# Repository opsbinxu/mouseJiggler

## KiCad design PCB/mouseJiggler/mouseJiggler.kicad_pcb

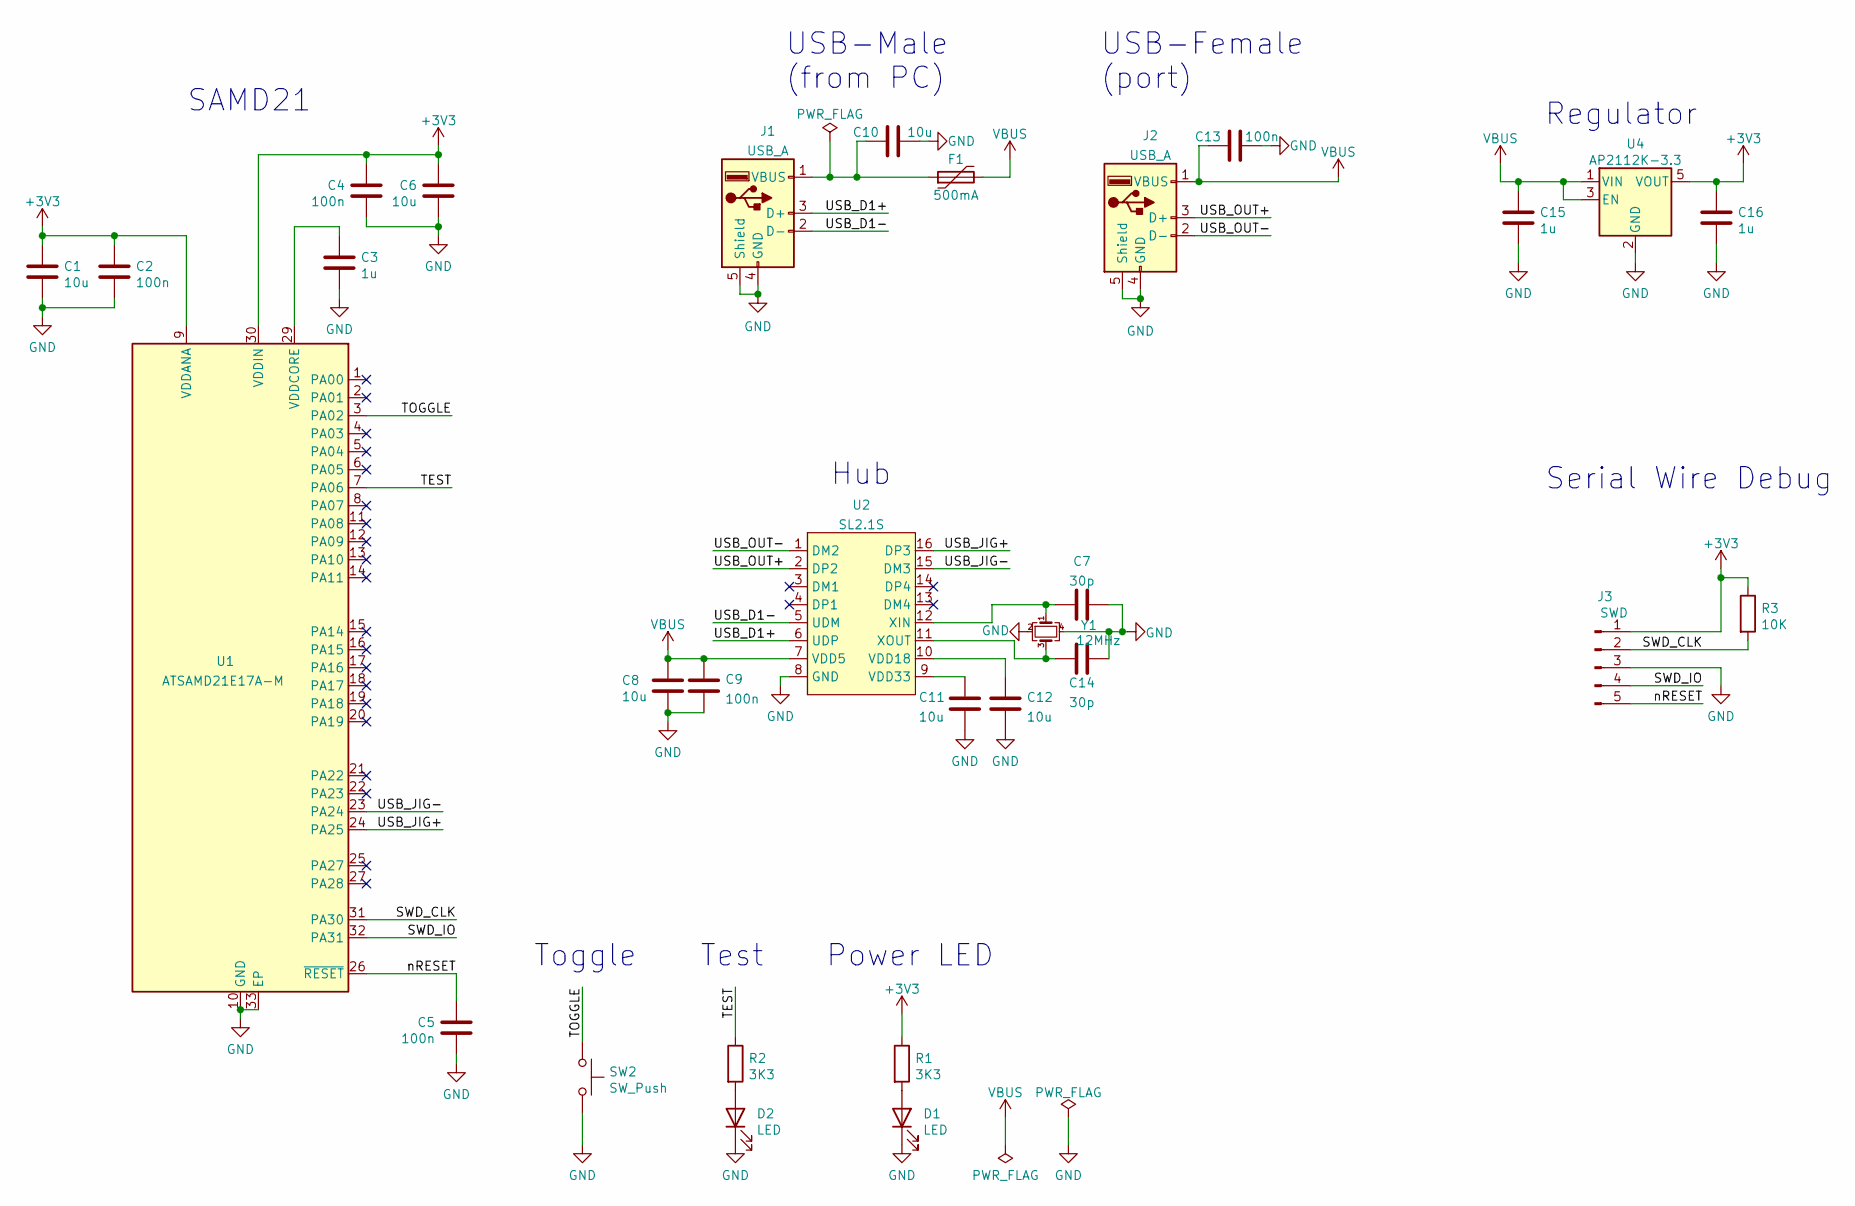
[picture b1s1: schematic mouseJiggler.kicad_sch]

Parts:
C1, C6, C8, C10: 10u; C_0603_1608Metric
C2, C4, C5, C9, C13: 100n; C_0402_1005Metric
C3, C15, C16: 1u; C_0402_1005Metric
C7, C14: 30p; C_0402_1005Metric
C11, C12: 10u; C_0402_1005Metric
D1, D2: LED; LED_0603_1608Metric
F1: 500mA; Fuse_0603_1608Metric
J1: USB_A; USB_A_CNCTech_1001-011-01101_Horizontal
J2: USB_A; USB_A_Molex_67643_Horizontal
J3: SWD; 5_PIN_SMD_PROG
R1, R2: 3K3; C_0402_1005Metric
R3: 10K; C_0402_1005Metric
SW2: SW_Push; SW_PUSH_EVQPUL_EVQPUC
U1: ATSAMD21E17A-M; QFN-32-1EP_5x5mm_P0.5mm_EP3.6x3.6mm
U2: SL2.1S; SSOP-16_4.6x2.6mm_P0.53
U4: AP2112K-3.3; SOT-23-5
Y1: 12MHz; Crystal_SMD_2520-4Pin_2.5x2.0mm

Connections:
+3V3: C1.1, C2.1, C4.1, C6.1, C16.1, J3.1, R1.1, R3.1, U1.9 (VDDANA), U1.30 (VDDIN), U4.5 (VOUT)
/SWD_CLK: J3.2, R3.2, U1.31 (PA30)
/SWD_IO: J3.4, U1.32 (PA31)
/TEST: R2.1, U1.7 (PA06)
/TOGGLE: SW2.1, U1.3 (PA02)
/USB_D1+: J1.3 (D+), U2.6 (UDP)
/USB_D1-: J1.2 (D-), U2.5 (UDM)
/USB_JIG+: U1.24 (PA25), U2.16 (DP3)
/USB_JIG-: U1.23 (PA24), U2.15 (DM3)
/USB_OUT+: J2.3 (D+), U2.2 (DP2)
/USB_OUT-: J2.2 (D-), U2.1 (DM2)
/nRESET: C5.1, J3.5, U1.26 (~RESET)
GND: C1.2, C2.2, C3.2, C4.2, C5.2, C6.2, C7.2, C8.2, C9.2, C10.2, C11.1, C12.2, C13.2, C14.2, C15.2, C16.2, D1.1 (K), D2.1 (K), J1.4 (GND), J1.5 (Shield), J2.4 (GND), J2.5 (Shield), J3.3, SW2.2, U1.10 (GND), U1.28 (GND), U1.33 (EP), U2.8 (GND), U4.2 (GND), Y1.2, Y1.4
unnamed: C3.1, U1.29 (VDDCORE)
unnamed: C7.1, U2.12 (XIN), Y1.1
unnamed: C10.1, F1.1, J1.1 (VBUS)
unnamed: C11.2, U2.9 (VDD33)
unnamed: C12.1, U2.10 (VDD18)
unnamed: C14.1, U2.11 (XOUT), Y1.3
unnamed: D1.2 (A), R1.2
unnamed: D2.2 (A), R2.2
VBUS: C8.1, C9.1, C13.1, C15.1, F1.2, J2.1 (VBUS), U2.7 (VDD5), U4.1 (VIN), U4.3 (EN)

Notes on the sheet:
SAMD21
Toggle
Test
USB-Male (from PC)
Power LED
Hub
USB-Female (port)
Regulator
Serial Wire Debug

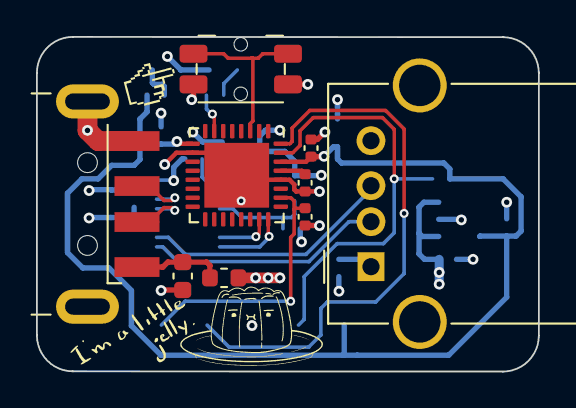
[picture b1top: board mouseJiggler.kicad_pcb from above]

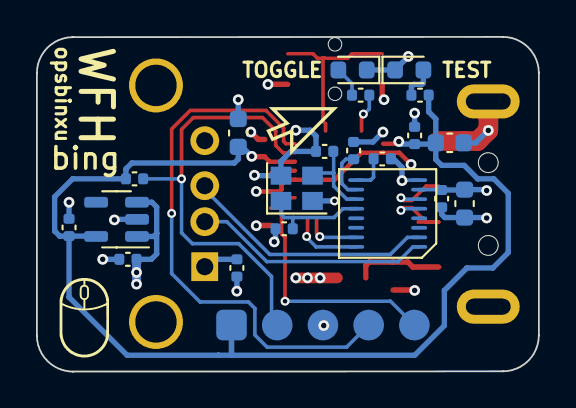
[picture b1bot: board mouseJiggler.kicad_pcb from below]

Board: 4 copper layers, 27.9 x 18.6 mm, 30 parts (21 on the bottom side), 22 nets.

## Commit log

2021-09-01 Schematic
2021-09-03 Update Schematic
2021-09-03 Added my library as submodule
2021-09-03 Create hub footprint
2021-09-04 Updated schematic
2021-09-04 Update crystal footprint
2021-09-05 Update PCB
2021-09-05 Added test LED and updated PCB
2021-09-05 Fix DRC issues
2023-05-25 Case STEP files and debug notes
